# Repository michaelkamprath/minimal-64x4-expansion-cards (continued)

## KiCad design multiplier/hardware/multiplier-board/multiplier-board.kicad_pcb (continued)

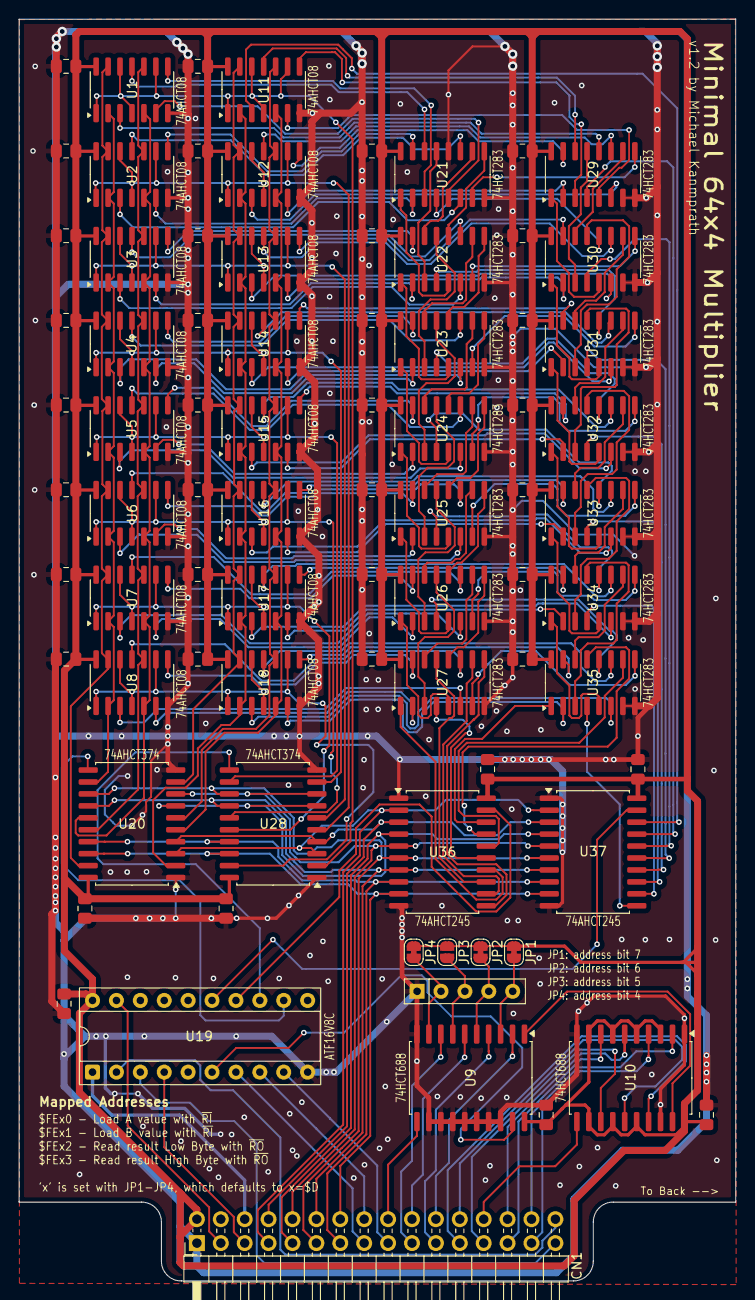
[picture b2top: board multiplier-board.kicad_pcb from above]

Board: 2 copper layers, 76.2 x 134.1 mm, 80 parts (0 on the bottom side), 191 nets.

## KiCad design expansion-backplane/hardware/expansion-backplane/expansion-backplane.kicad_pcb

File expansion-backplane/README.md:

# Expansion Backplane for Minimal 64x4 Computer

This backplane allows connecting of up to 4 expansion cards to the Minimal 64x4 computer. The [expansion connector](./hardware/expansion-connector/) is a convenient way to connect the backplane to the Minimal 64x4 computer.

### Shared `INH` Line
To have multiple cards connected to the backplane, they need to share the active high `INH` inhibit line. If multiple cards are emitting a LOW signal directly, and one emits a HIGH, contention will occur. To prevent such contention, the back plane uses a 74AHCT126 to arbitrate the `INH` signal's progression from a card to the Minimal 64x4's exansion port. Each of the buffers in the 74AHCT126 have their input signal tied high, and the each card's `INH` output us used to control the output enable for it's assigned buffer. In this way, when a card's `INH` output is low (not active), it's corresponding buffer has its output in a high-Z state. So if another card asserts it's `INH` line high, there won't be bus contention back to the card. But each card's active high `INH` signal is passed through to the Minimal 64x4. The downside is that each expansion card cannot monitor whether another card is asserting the `INH` signal. This is not deemed to be a signficant issues since Minimal 64x4 expansion board are generally memory mapped, and thus only one can be actively writing to the bus at a time.

### Card Address Assignment
The data bus has **no arbitration** — the `INH` scheme above protects only the inhibit line. Correctness depends entirely on one card decoding a given address. Because address lines settle at different times during a bus transition, a card can transiently match another card's address and drive the bus against it, so assign base addresses to maximize the **Hamming distance of the decoded address bits**, not the hex separation.

| Card | Base | Decoded `A7..A3` |
| --- | --- | --- |
| Multiplier | `$FED0` | `11010` |
| Timer | `$FE28` | `00101` |

**Failure signature** (seen 2026-08 with the timer at `$FEF0`, one bit from the multiplier): reads from the victim card return wrong values intermittently, writes and RAM are fine, results vary run to run *and* between builds as code shifts, and software-only builds are perfect. Diagnose by moving one card, not by debugging the software.

Two mechanisms produce this and are **not yet distinguished**: address-line skew, or the 74HCT688 comparator glitching its output during input transitions. If it's the latter, bit distance is only probabilistic protection and a gated `/G` or delayed enable is needed. To measure: reinstate the colliding address, run `multiplier/software/test_karatsuba_layers.min64x4` (fails ~30% of 65536 cases, so events are continuous), and trigger a logic analyzer on *the victim card's decode asserting while the address belongs to the other card*.

Note that CLK-gating a card's read output enable is **not** a fix: the address and `RI`/`RO` are set on the falling edge and the selected card must be driving the bus before the rising edge latches it, so the read enable has to be live during the settling window by design.

### Power Barrel Jack
The back plane provides a convenient standard 2.1 mm barrel jack you may use to connect to a regulated `5V` power supply to power the expansion cards and additionally power the Minimal 64x4 computer. If this barrel jack is connected to power, be sure to not connect the UART's `+5V` line to the Minimal 64x4 (still connect `GND`)

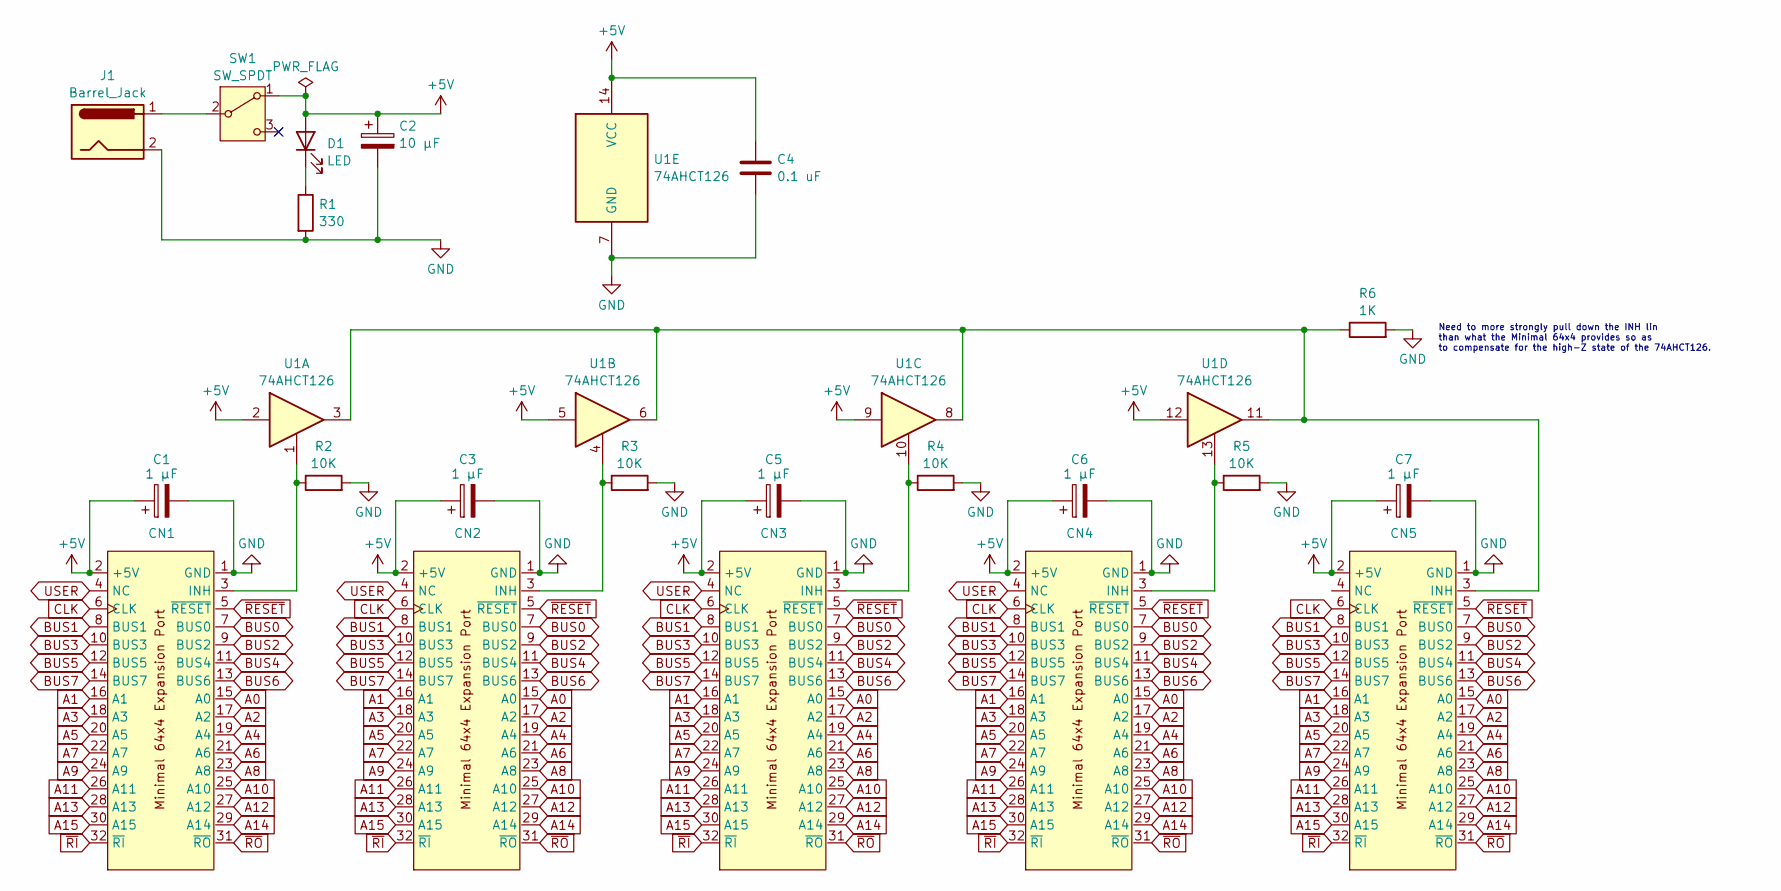
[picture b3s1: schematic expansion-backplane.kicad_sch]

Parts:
C1, C3, C5, C6, C7: 1 µF; CP_Radial_D4.0mm_P2.00mm
C2: 10 µF; CP_Radial_D5.0mm_P2.00mm
C4: 0.1 uF; C_Disc_D3.8mm_W2.6mm_P2.50mm
CN1, CN2, CN3, CN4, CN5: PinSocket_2x16_P2.54mm_Vertical
D1: LED; LED_D3.0mm
J1: Barrel_Jack; BarrelJack_Horizontal
R1: 330; R_Axial_DIN0207_L6.3mm_D2.5mm_P7.62mm_Horizontal
R2, R3, R4, R5: 10K; R_Axial_DIN0207_L6.3mm_D2.5mm_P7.62mm_Horizontal
R6: 1K; R_Axial_DIN0207_L6.3mm_D2.5mm_P7.62mm_Horizontal
SW1: SW_SPDT; E-Switch_200MSP1T2B2M6RE
U1: 74AHCT126; DIP-14_W7.62mm

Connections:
+5V: C1.1, C2.1, C3.1, C4.1, C5.1, C6.1, C7.1, CN1.2 (+5V), CN2.2 (+5V), CN3.2 (+5V), CN4.2 (+5V), CN5.2 (+5V), D1.2 (A), SW1.1 (A), U1.2, U1.5, U1.9, U1.12, U1.14 (VCC)
A0: CN1.15 (A0), CN2.15 (A0), CN3.15 (A0), CN4.15 (A0), CN5.15 (A0)
A1: CN1.16 (A1), CN2.16 (A1), CN3.16 (A1), CN4.16 (A1), CN5.16 (A1)
A2: CN1.17 (A2), CN2.17 (A2), CN3.17 (A2), CN4.17 (A2), CN5.17 (A2)
A3: CN1.18 (A3), CN2.18 (A3), CN3.18 (A3), CN4.18 (A3), CN5.18 (A3)
A4: CN1.19 (A4), CN2.19 (A4), CN3.19 (A4), CN4.19 (A4), CN5.19 (A4)
A5: CN1.20 (A5), CN2.20 (A5), CN3.20 (A5), CN4.20 (A5), CN5.20 (A5)
A6: CN1.21 (A6), CN2.21 (A6), CN3.21 (A6), CN4.21 (A6), CN5.21 (A6)
A7: CN1.22 (A7), CN2.22 (A7), CN3.22 (A7), CN4.22 (A7), CN5.22 (A7)
A8: CN1.23 (A8), CN2.23 (A8), CN3.23 (A8), CN4.23 (A8), CN5.23 (A8)
A9: CN1.24 (A9), CN2.24 (A9), CN3.24 (A9), CN4.24 (A9), CN5.24 (A9)
A10: CN1.25 (A10), CN2.25 (A10), CN3.25 (A10), CN4.25 (A10), CN5.25 (A10)
A11: CN1.26 (A11), CN2.26 (A11), CN3.26 (A11), CN4.26 (A11), CN5.26 (A11)
A12: CN1.27 (A12), CN2.27 (A12), CN3.27 (A12), CN4.27 (A12), CN5.27 (A12)
A13: CN1.28 (A13), CN2.28 (A13), CN3.28 (A13), CN4.28 (A13), CN5.28 (A13)
A14: CN1.29 (A14), CN2.29 (A14), CN3.29 (A14), CN4.29 (A14), CN5.29 (A14)
A15: CN1.30 (A15), CN2.30 (A15), CN3.30 (A15), CN4.30 (A15), CN5.30 (A15)
BUS0: CN1.7 (BUS0), CN2.7 (BUS0), CN3.7 (BUS0), CN4.7 (BUS0), CN5.7 (BUS0)
BUS1: CN1.8 (BUS1), CN2.8 (BUS1), CN3.8 (BUS1), CN4.8 (BUS1), CN5.8 (BUS1)
BUS2: CN1.9 (BUS2), CN2.9 (BUS2), CN3.9 (BUS2), CN4.9 (BUS2), CN5.9 (BUS2)
BUS3: CN1.10 (BUS3), CN2.10 (BUS3), CN3.10 (BUS3), CN4.10 (BUS3), CN5.10 (BUS3)
BUS4: CN1.11 (BUS4), CN2.11 (BUS4), CN3.11 (BUS4), CN4.11 (BUS4), CN5.11 (BUS4)
BUS5: CN1.12 (BUS5), CN2.12 (BUS5), CN3.12 (BUS5), CN4.12 (BUS5), CN5.12 (BUS5)
BUS6: CN1.13 (BUS6), CN2.13 (BUS6), CN3.13 (BUS6), CN4.13 (BUS6), CN5.13 (BUS6)
BUS7: CN1.14 (BUS7), CN2.14 (BUS7), CN3.14 (BUS7), CN4.14 (BUS7), CN5.14 (BUS7)
CLK: CN1.6 (CLK), CN2.6 (CLK), CN3.6 (CLK), CN4.6 (CLK), CN5.6 (CLK)
GND: C1.2, C2.2, C3.2, C4.2, C5.2, C6.2, C7.2, CN1.1 (GND), CN2.1 (GND), CN3.1 (GND), CN4.1 (GND), CN5.1 (GND), J1.2, R1.2, R2.2, R3.2, R4.2, R5.2, R6.2, U1.7 (GND)
unnamed: CN1.3 (INH), R2.1, U1.1
unnamed: CN2.3 (INH), R3.1, U1.4
unnamed: CN3.3 (INH), R4.1, U1.10
unnamed: CN4.3 (INH), R5.1, U1.13
unnamed: CN5.3 (INH), R6.1, U1.3, U1.6, U1.8, U1.11
unnamed: D1.1 (K), R1.1
unnamed: J1.1, SW1.2 (B)
USER: CN1.4 (NC), CN2.4 (NC), CN3.4 (NC), CN4.4 (NC)
~RESET: CN1.5 (~RESET), CN2.5 (~RESET), CN3.5 (~RESET), CN4.5 (~RESET), CN5.5 (~RESET)
~RI: CN1.32 (~RI), CN2.32 (~RI), CN3.32 (~RI), CN4.32 (~RI), CN5.32 (~RI)
~RO: CN1.31 (~RO), CN2.31 (~RO), CN3.31 (~RO), CN4.31 (~RO), CN5.31 (~RO)

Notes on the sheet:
Need to more strongly pull down the INH lin than what the Minimal 64x4 provides so as to compensate for the high-Z state of the 74AHCT126.

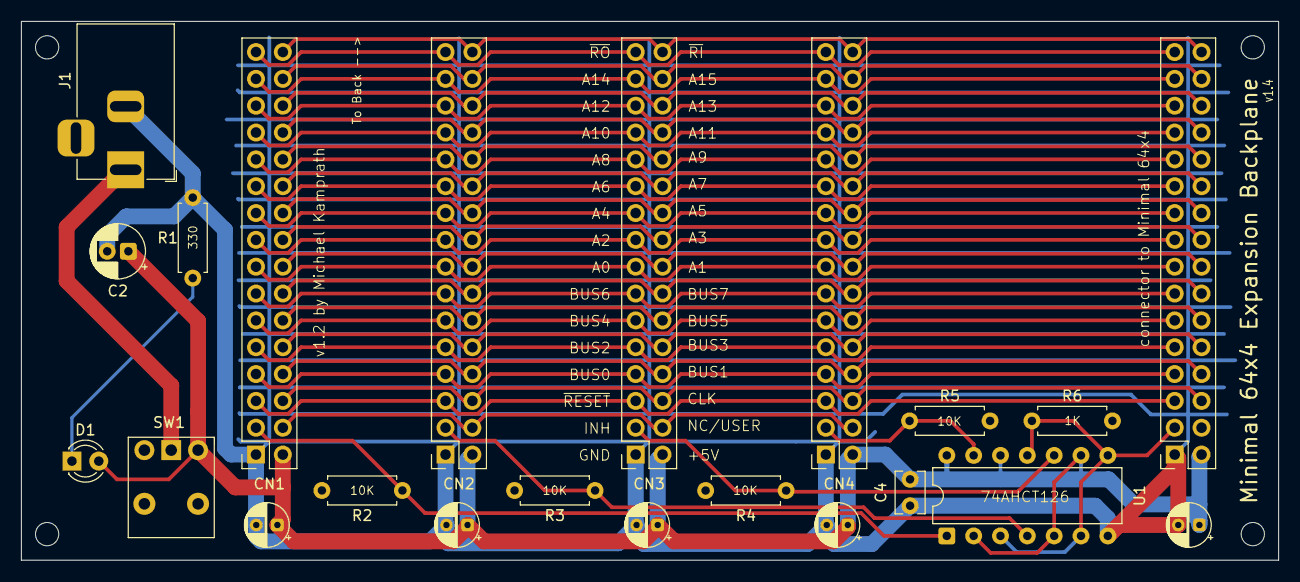
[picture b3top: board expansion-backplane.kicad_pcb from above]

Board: 2 copper layers, 119.0 x 51.0 mm, 22 parts (0 on the bottom side), 38 nets.

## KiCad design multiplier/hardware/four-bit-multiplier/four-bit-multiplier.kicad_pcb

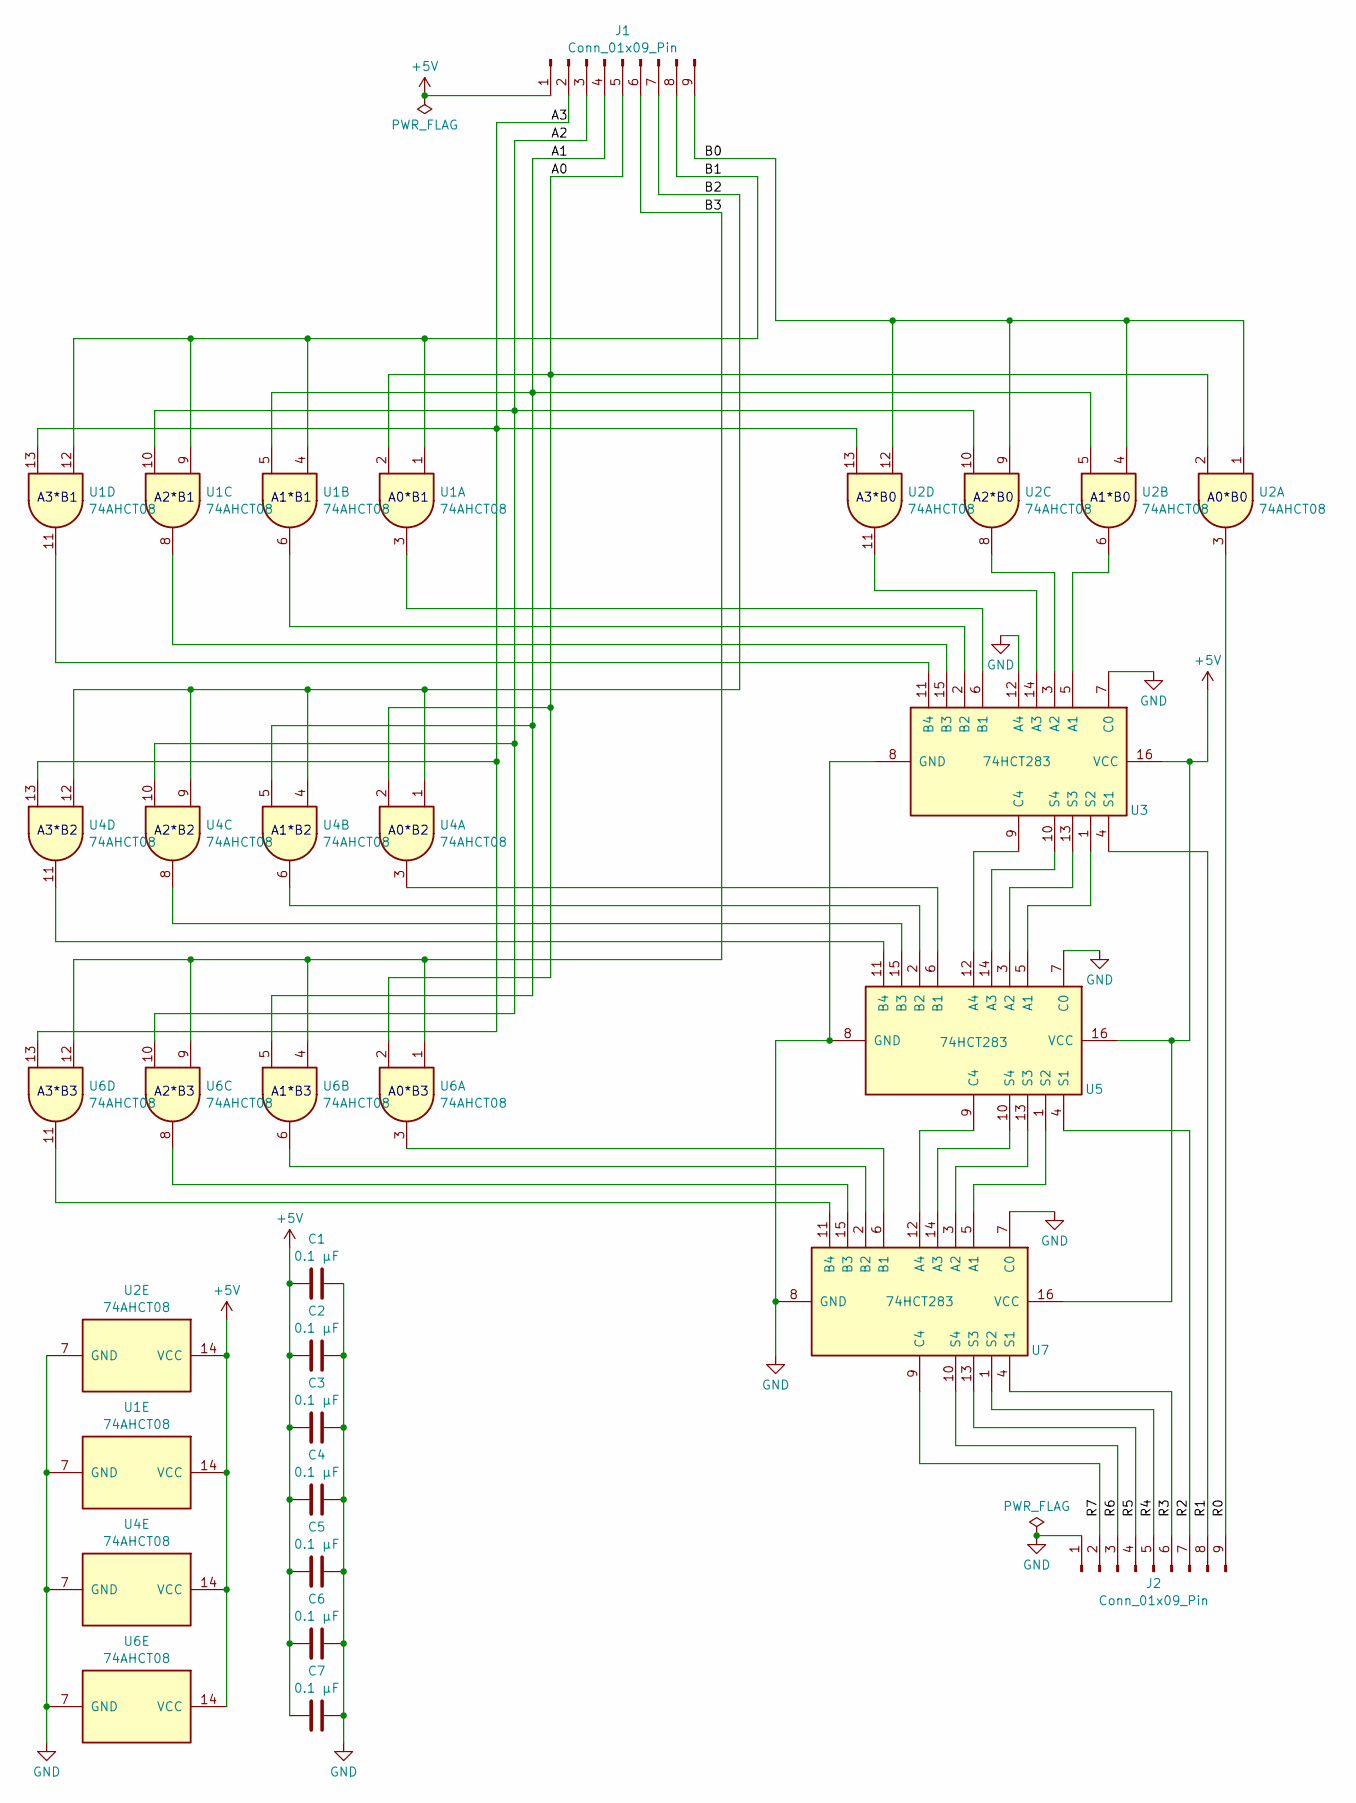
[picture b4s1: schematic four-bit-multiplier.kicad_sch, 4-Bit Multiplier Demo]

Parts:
C1, C2, C3, C4, C5, C6, C7: 0.1 µF; C_0805_2012Metric_Pad1.18x1.45mm_HandSolder
J1, J2: Conn_01x09_Pin; PinHeader_1x09_P2.54mm_Vertical
U1, U2, U4, U6: 74AHCT08; SOIC-14_3.9x8.7mm_P1.27mm
U3, U5, U7: 74HCT283; SOIC-16_3.9x9.9mm_P1.27mm

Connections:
+5V: C1.1, C2.1, C3.1, C4.1, C5.1, C6.1, C7.1, J1.1, U1.14 (VCC), U2.14 (VCC), U3.16 (VCC), U4.14 (VCC), U5.16 (VCC), U6.14 (VCC), U7.16 (VCC)
/A0: J1.5, U1.2, U2.2, U4.2, U6.2
/A1: J1.4, U1.5, U2.5, U4.5, U6.5
/A2: J1.3, U1.10, U2.10, U4.10, U6.10
/A3: J1.2, U1.13, U2.13, U4.13, U6.13
/B0: J1.9, U2.1, U2.4, U2.9, U2.12
/B1: J1.8, U1.1, U1.4, U1.9, U1.12
/B2: J1.7, U4.1, U4.4, U4.9, U4.12
/B3: J1.6, U6.1, U6.4, U6.9, U6.12
/R0: J2.9, U2.3
/R1: J2.8, U3.4 (S1)
/R2: J2.7, U5.4 (S1)
/R3: J2.6, U7.4 (S1)
/R4: J2.5, U7.1 (S2)
/R5: J2.4, U7.13 (S3)
/R6: J2.3, U7.10 (S4)
/R7: J2.2, U7.9 (C4)
GND: C1.2, C2.2, C3.2, C4.2, C5.2, C6.2, C7.2, J2.1, U1.7 (GND), U2.7 (GND), U3.7 (C0), U3.8 (GND), U3.12 (A4), U4.7 (GND), U5.7 (C0), U5.8 (GND), U6.7 (GND), U7.7 (C0), U7.8 (GND)
unnamed: U2.6, U3.5 (A1)
unnamed: U2.8, U3.3 (A2)
unnamed: U2.11, U3.14 (A3)
unnamed: U1.3, U3.6 (B1)
unnamed: U1.6, U3.2 (B2)
unnamed: U1.8, U3.15 (B3)
unnamed: U1.11, U3.11 (B4)
unnamed: U3.9 (C4), U5.12 (A4)
unnamed: U3.1 (S2), U5.5 (A1)
unnamed: U3.13 (S3), U5.3 (A2)
unnamed: U3.10 (S4), U5.14 (A3)
unnamed: U4.3, U5.6 (B1)
unnamed: U4.6, U5.2 (B2)
unnamed: U4.8, U5.15 (B3)
unnamed: U4.11, U5.11 (B4)
unnamed: U5.9 (C4), U7.12 (A4)
unnamed: U5.1 (S2), U7.5 (A1)
unnamed: U5.13 (S3), U7.3 (A2)
unnamed: U5.10 (S4), U7.14 (A3)
unnamed: U6.3, U7.6 (B1)
unnamed: U6.6, U7.2 (B2)
unnamed: U6.8, U7.15 (B3)
unnamed: U6.11, U7.11 (B4)

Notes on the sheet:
A3*B3
A1*B2
A1*B0
A0*B0
A2*B2
A2*B1
A1*B1
A1*B3
A2*B0
A3*B2
A2*B3
A0*B3
A3*B1
A3*B0
A0*B2
A0*B1

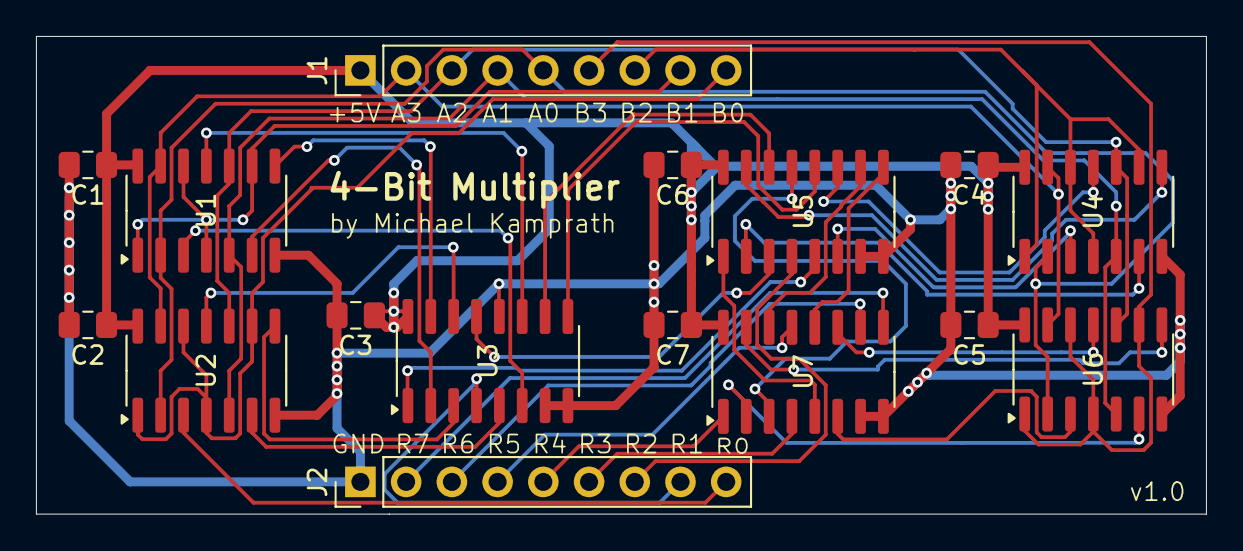
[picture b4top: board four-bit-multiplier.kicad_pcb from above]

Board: 2 copper layers, 65.0 x 26.5 mm, 16 parts (0 on the bottom side), 41 nets.

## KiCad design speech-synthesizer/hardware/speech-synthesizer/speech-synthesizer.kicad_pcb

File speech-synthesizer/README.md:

# TMS5220 Speech Synthesizer for Minimal 64x4 Computer
This project creates a TMS5220-based speech synthesizer board for the [Minimal 64x4](https://github.com/slu4coder/Minimal-64x4-Home-Computer) expansion port. The high-level design criteria are:

1. **Accommodate the “slow memory” nature of the TMS5220** by using hardware to buffer the interactions between the CPU and the TMS5220 such that the CPU is free to do other tasks while the TMS5220 processes data. This contrasts with typical 1980s computer hardware designs, which would halt the CPU while the TMS5220 processed data.
2. **Only support “external” speech data; PHROMs are not supported.** Not supporting PHROMs greatly simplifies the board and saves money, as original PHROMs are hard to come by in the modern age. Most games of the 1980s did not use PHROM data, instead providing their own LPC-encoded speech data.

This board supports both the TMS5220 and TMS5220C variants of the speech synthesizer chip.

## Hardware Design
The board responds to three memory-mapped addresses (the board is adjustable to set the `_` value below, but it defaults to `0xC`):

* `0xFE_0` – **TMS5220 Command Register**
  This address allows the host computer to write data to the TMS5220’s command register, which is used for sending “external speech” data to the TMS5220. In general, the host computer will write certain TMS5220 commands and speech data to this address.

* `0xFE_1` – **TMS5220 Status Register**
  This address allows the host computer to fetch the internal TMS5220 status register. To do that, the host computer writes some data to this address (any value, as the value is not actually used) to start the sequence of events to get the internal status from the TMS5220. When this is done, the status value will be readable by the host computer at this address. The status data being ready is indicated by the board’s `BUSY` line, which is readable at the **Board Status Register**. The `BUSY` line will be asserted high from the moment this address is written to until the status value is ready to be read.

* `0xFE_2` – **Board Status Register**
  This address exposes several internal states of this board, independent of the TMS5220, and can be read by the host computer at any time. The individual bits within the byte value read are below. Of these lines, the host computer generally only interacts with the `/INT` and `BUSY` bits.

  * **bit 0 – `BUSY`**
    Indicates whether the TMS5220 or the board, in general, is working on something. The host computer should not interact with the TMS5220 Command or Status registers while this bit is high.
  * **bit 1 – `/INT`**
    The current value of the active-low interrupt line coming out of the TMS5220. When this bit is low, it indicates that the TMS5220 requires attention. The specific issue can be determined by reading the TMS5220 Status Register.
  * **bit 2 – `/READY`**
    The current value of the active-low `READY` line out of the TMS5220. Host computer software should use the `BUSY` line to arbitrate interaction with the board, but the `READY` line is exposed here for diagnostic purposes.
  * **bit 3 – `WS`**
    The current status of the `WS` flip flop (active high). Exposed for diagnostic purposes.
  * **bit 4 – `RS`**
    The current status of the `RS` flip flop (active high). Exposed for diagnostic purposes.

* `0xFE_3` – **TMS5220C Reset** – *Currently Unimplemented*
  The TMS5220C variant can be reset by holding both the `/RS` and `/WS` lines low at the same time. This action has undefined results for the non-C TMS5220 variant.

### TMS5220 “Slow Memory” Issue
A key pin to understand on the TMS5220 is the `READY` signal at pin 18. The TMS5220 drives the `READY` pin low when it is ready to accept input or provide output to the host computer. When the `READY` pin is high, the TMS5220 is busy processing data and does not immediately act on—if not outright ignore—any interactions the CPU initiates. In many 1980s-era computers, the `READY` pin was connected to the CPU’s halt or wait-state pin, causing the CPU to stop while the TMS5220 processed data. This board takes a different approach. In some ways, this is necessary because the Minimal 64x4 has no line that would allow an accessory to pause or halt the CPU. However, this design choice is otherwise agnostic of that limitation.

As a result, data interactions between the host computer and the TMS5220 must be cached to handle the timing differences. The key to caching these CPU interactions is the ATF22V10C programmable logic chip and the 74HCT74 flip flops. The flip flops hold the `/WS` and `/RS` signals on the TMS5220, and the ATF22V10C is programmed to create a state machine that manages these flip flops. For example, here is the sequence of events for writing a byte of data to the TMS5220:

1. When the address bus is set to the memory-mapped address of `0xFEC0`, the 74HCT688s will assert this `MMAP` line, and the `M0` and `M1` address lines will be 0. To write to the TMS5220, the host computer `/RI` line will be asserted. The ATF22V10C’s programmable logic then asserts `WS_CLK`, which is the clock line that drives the `WS` flip flop, in turn asserting the active-low `/WS` line to the TMS5220. This tells the TMS5220 that we want to write data to its data lines.
2. At the same time `WS_CLK` causes the `WS` flip flop to set its state, `WS_CLK` also causes the data bus input 74HCT374 flip flop to load the contents of the host computer’s data bus. Because of this, the expansion board can capture and hold the data bus value the host computer is writing to the TMS5220, allowing the host computer to move on to other tasks while this flip flop holds the data bus value. Furthermore, the `/WS` line to the TMS5220 also drives the output enable on the 74HCT374 octal flip flop, so the buffered data will be held and driven onto the board’s internal data bus for the entire time `/WS` is low—even as the host computer does other work. This is the essence of the “slow memory” issue: the TMS5220 requires several host-computer clock cycles to read in the data, and its data lines must be held for the entire duration. The 74HCT374 flip flop buffers the data and holds the lines active as long as needed.
3. In response to the `/WS` line being asserted, the TMS5220 drives the `READY` line high. When this occurs, the ATF22V10C waits until the `READY` line transitions from high to low, which indicates that the TMS5220 has finished processing the input data. When the `READY` line goes low, the ATF22V10C then asserts `WS_RST`, the reset line for the `WS` flip flop. This brings `/WS` high, which tells the TMS5220 that the write operation is complete. It also disables the output enable on the 74HCT374 that was buffering the data. In this way, `/WS` remains asserted until the TMS5220 indicates it is done reading the data from the buffers, as indicated by the `READY` line.
4. During this entire sequence, the ATF22V10C asserts the `BUSY` line for the board, which can be read by the host computer at address `0xFE_2` via the 74HCT245. This allows the host computer to query the board to see if the TMS5220 is done processing data.

A similar sequence is used when reading data from the TMS5220, centered around the `/RS` line.

### Undocumented Timing Issues
The TMS5220 appears to have some timing requirements that are not documented in its datasheet. These requirements were exposed by the Minimal 64x4, which runs at a clock speed faster than the typical host computers for which the TMS5220 was designed. These undocumented timing requirements were determined empirically and could likely be tweaked further:

* **Read Cycle for Status Transfers to External Speech Data Write**
  The datasheet indicates that the `t_wait` after `/RS` goes high is 12 µs. However, I found that something closer to 175 µs was needed between a status read and a subsequent external speech data write.

* **External Speech Data Write to Read Cycle for Status Transfers**
  Similarly, extra time is needed between writing external speech data and then reading the TMS5220 status. Again, I found that about 175 µs was needed.

These values were “tweaked until it worked.” The issues seem related to switching modes of interaction with the TMS5220. By contrast, writing an external speech data byte after a prior external speech data byte does adhere to the timing diagrams in the TMS5220 datasheet. Further experimentation might uncover better or smaller delays for these undocumented requirements.

## Software Design
The provided `speechlib.min64x4` file contains all the subroutines needed to use this board on the Minimal 64x4 home computer:

* `speech_init`
  Call this to initialize the board.

* `speak_synchronous`
  Speaks the LPC data in a passed buffer synchronously. Push the following arguments on the stack (in push order):
  1. **Buffer End Address** – 2-byte end address of the data buffer
  2. **Buffer Start Address** – 2-byte start address of the data buffer

* `speech_start`
  Speaks the LPC data in a passed buffer asynchronously, after synchronously waiting for any currently active talking to finish. Push the following arguments on the stack (in push order):
  1. **Buffer End Address** – 2-byte end address of the data buffer
  2. **Buffer Start Address** – 2-byte start address of the data buffer

* `speech_start_if_not_talking`
  Speaks the LPC data in a passed buffer asynchronously if there is no currently active speech. Push the following arguments on the stack (in push order):
  1. **Buffer End Address** – 2-byte end address of the data buffer
  2. **Buffer Start Address** – 2-byte start address of the data buffer

* `speech_update_buffer`
  Call this periodically (about every 1 ms) to enable asynchronous speech. No arguments.

* `speech_get_status`
  Gets the contents of the TMS5220 status register, which is returned in the `A` register. The following bit masks are defined to help interpret the results:
  * `SPEECH_STATUS_TALK` – The TMS5220 is currently talking.
  * `SPEECH_STATUS_BUFFER_LOW` – The TMS5220 FIFO buffer is half-empty. More LPC data needs to be sent.
    *_Note_*: The `speech_update_buffer` function automatically updates the FIFO if needed.
  * `SPEECH_STATUS_BUFFER_EMPTY` – The TMS5220 FIFO buffer is empty.

# Compiling the Software
All software found in the [software](./software/) directory is compiled with [BespokeASM](https://github.com/michaelkamprath/bespokeasm), which supports the Minimal 64x4. [Carsten Herting](https://github.com/slu4coder), the creator of the Minimal 64x4, also provides an assembler for it, but that assembler is quite minimal. One key shortcoming is the inability to import library code into the current compilation. BespokeASM enables importing libraries and includes several other features that this project’s software depends on.

To compile the speech code in this repository, use the following command:

```sh
bespokeasm compile -c /path/to/bespokeasm/examples/slu4-minimal-64x4/slu4-minimal-64x4.yaml -n -p -t intel_hex lpc_player.min64x4
```
Where `/path/to/bespokeasm` is the path to the BespokeASM repository on your computer. This will produce an Intel HEX representation of the compiled program, which can then be sent to the Minimal 64x4 using its `receive` command.

# Resources
The following resources I found useful when putting together this project

* [TMS5220 Datasheet](./datasheets/tms5220.pdf) - Always consult the datasheet first.
* [Thierry Nouspikel's "The Speech Synthesizer module"](https://www.unige.ch/medecine/nouspikel/ti99/speech.htm) - A detailed overview of how the TMS5220 is used in the TI 99/4a.
* [TI 99/4a Development forum on AtariAge](https://forums.atariage.com/topic/352156-looking-for-help-on-tms5220-circuit-software-design-and-usage/) - These folks are legends, helpful and knowledgable about anything related to Texas Instruments.

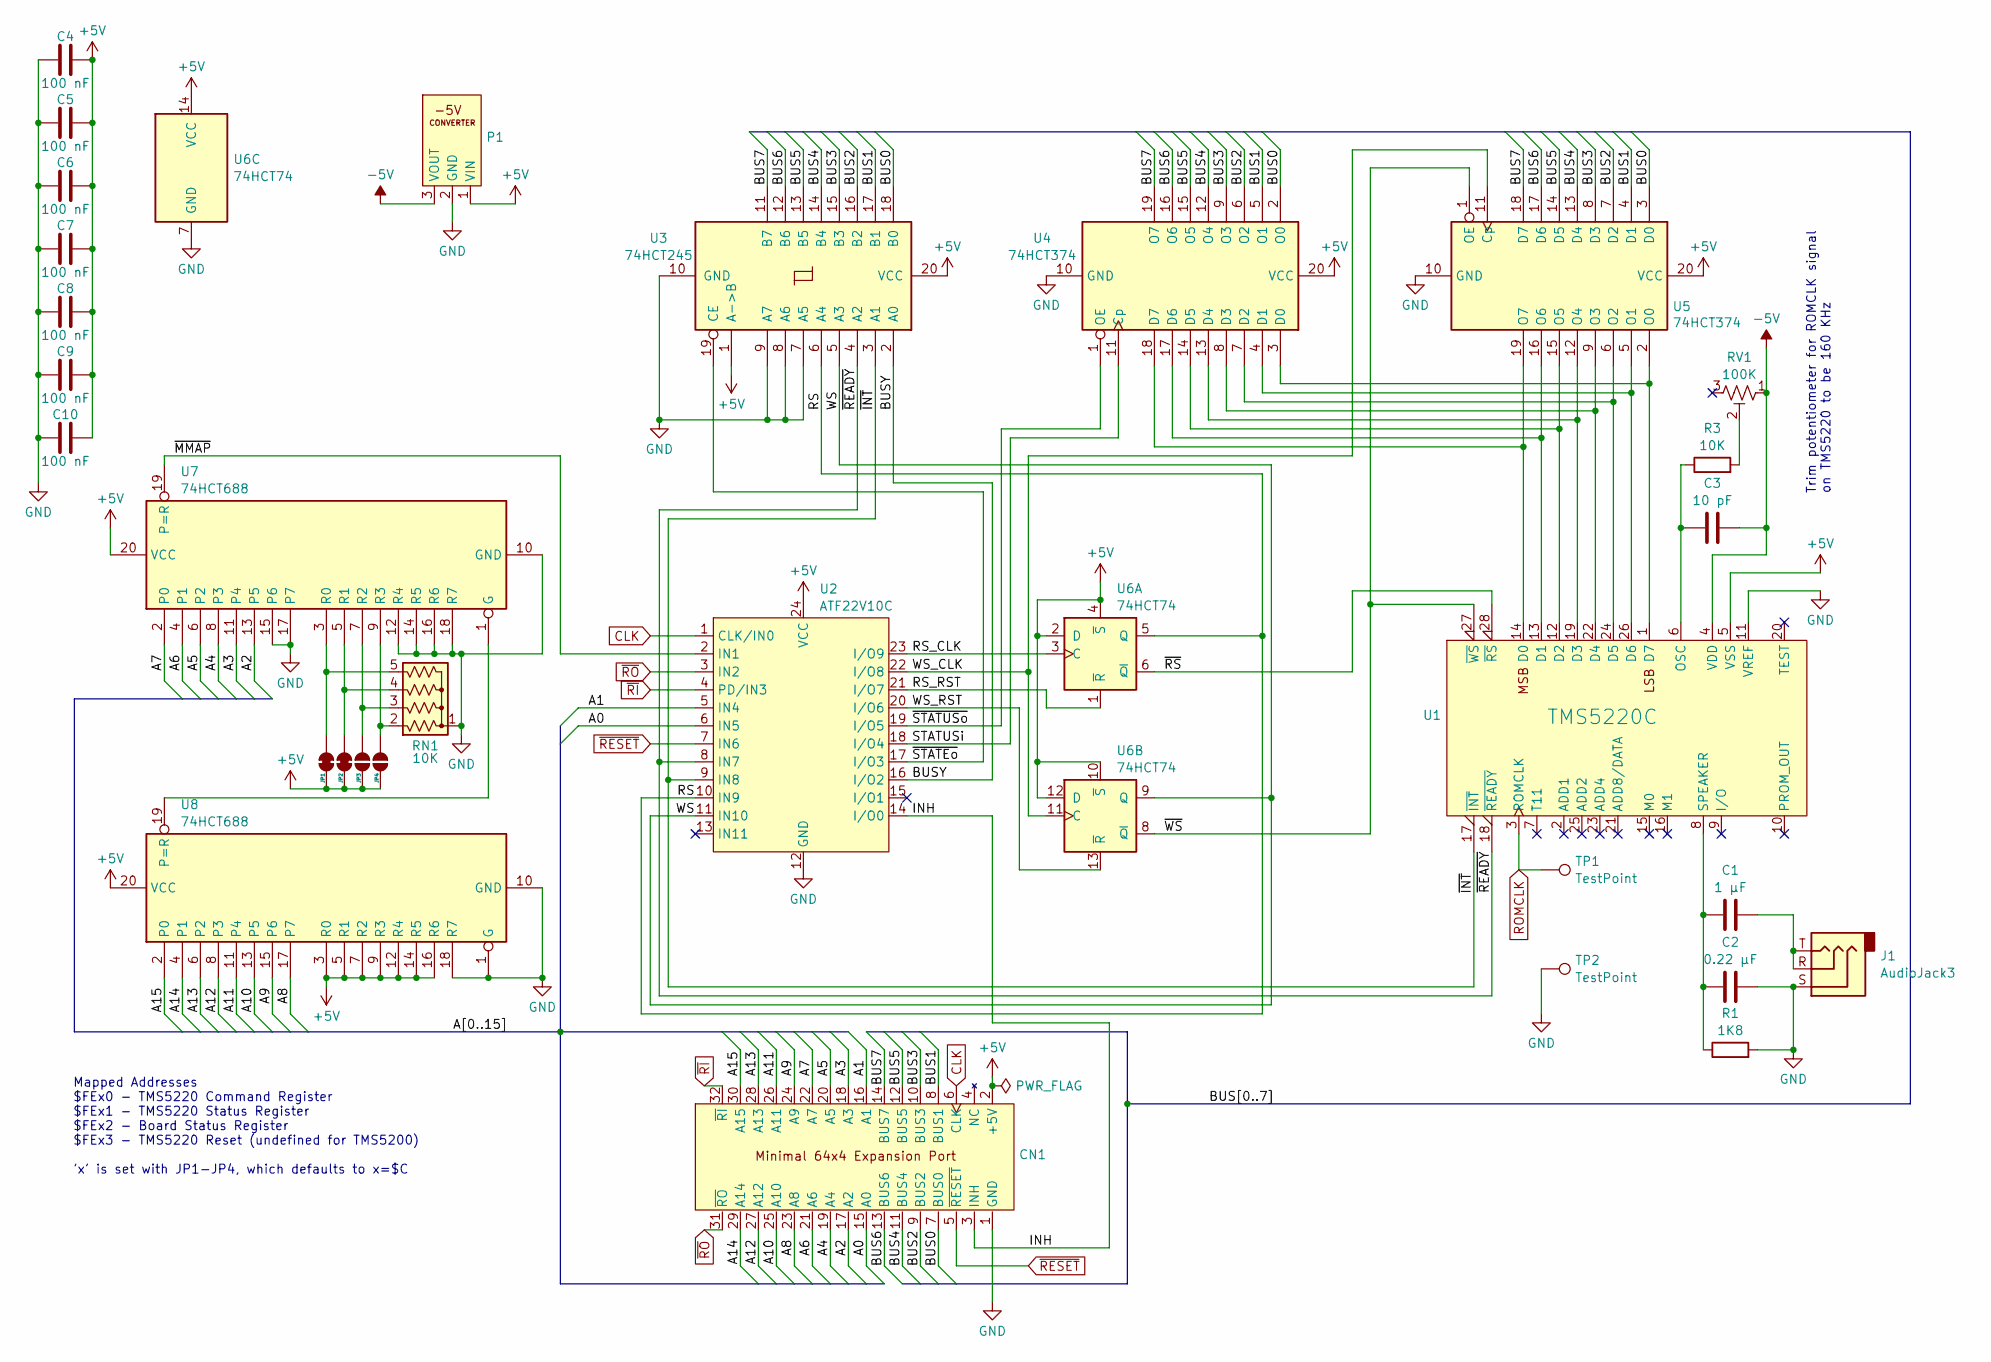
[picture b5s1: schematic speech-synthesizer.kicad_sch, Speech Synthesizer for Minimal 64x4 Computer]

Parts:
C1: 1 µF; C_Disc_D4.7mm_W2.5mm_P5.00mm
C2: 0.22 µF; C_Disc_D4.7mm_W2.5mm_P5.00mm
C3: 10 pF; C_Disc_D5.0mm_W2.5mm_P2.50mm
C4, C5, C6, C7, C8, C9, C10: 100 nF; C_Disc_D3.4mm_W2.1mm_P2.50mm
CN1: PinHeader_2x16_P2.54mm_Horizontal
J1: AudioJack3; Jack_3.5mm_CUI_SJ1-3523N_Horizontal
JP1, JP2: SolderJumper_2_Bridged; SolderJumper-2_P1.3mm_Bridged_RoundedPad1.0x1.5mm
JP3, JP4: SolderJumper_2_Open; SolderJumper-2_P1.3mm_Open_RoundedPad1.0x1.5mm
P1: -5V_Converter
R1: 1K8; R_Axial_DIN0207_L6.3mm_D2.5mm_P10.16mm_Horizontal
R3: 10K; R_Axial_DIN0207_L6.3mm_D2.5mm_P10.16mm_Horizontal
RN1: 10K; R_Array_SIP5
RV1: 100K; Potentiometer_Vishay_T73YP_Vertical
TP1, TP2: TestPoint; TestPoint_Pad_D2.0mm
U1: TMS5220C; DIP-28_W15.24mm_Socket
U2: ATF22V10C; DIP-24_W7.62mm_Socket
U3: 74HCT245; DIP-20_W7.62mm_Socket
U4, U5: 74HCT374; DIP-20_W7.62mm_Socket
U6: 74HCT74; DIP-14_W7.62mm_Socket
U7, U8: 74HCT688; DIP-20_W7.62mm_Socket

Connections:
+5V: C4.2, C5.2, C6.2, C7.2, C8.2, C9.2, C10.2, CN1.2 (+5V), JP1.1 (A), JP2.1 (A), JP3.1 (A), JP4.1 (A), P1.1 (VIN), U1.5 (VSS), U2.24 (VCC), U3.1 (A->B), U3.20 (VCC), U4.20 (VCC), U5.20 (VCC), U6.2 (D), U6.4 (~S), U6.10 (~S), U6.12 (D), U6.14 (VCC), U7.20 (VCC), U8.3 (R0), U8.5 (R1), U8.7 (R2), U8.9 (R3), U8.12 (R4), U8.14 (R5), U8.16 (R6), U8.20 (VCC)
-5V: C3.1, P1.3 (VOUT), RV1.1, U1.4 (VDD)
/A0: CN1.15 (A0), U2.6 (IN5)
/A1: CN1.16 (A1), U2.5 (IN4)
/A2: CN1.17 (A2), U7.13 (P5)
/A3: CN1.18 (A3), U7.11 (P4)
/A4: CN1.19 (A4), U7.8 (P3)
/A5: CN1.20 (A5), U7.6 (P2)
/A6: CN1.21 (A6), U7.4 (P1)
/A7: CN1.22 (A7), U7.2 (P0)
/A8: CN1.23 (A8), U8.17 (P7)
/A9: CN1.24 (A9), U8.15 (P6)
/A10: CN1.25 (A10), U8.13 (P5)
/A11: CN1.26 (A11), U8.11 (P4)
/A12: CN1.27 (A12), U8.8 (P3)
/A13: CN1.28 (A13), U8.6 (P2)
/A14: CN1.29 (A14), U8.4 (P1)
/A15: CN1.30 (A15), U8.2 (P0)
/BUS0: CN1.7 (BUS0), U3.18 (B0), U4.2 (O0), U5.3 (D0)
/BUS1: CN1.8 (BUS1), U3.17 (B1), U4.5 (O1), U5.4 (D1)
/BUS2: CN1.9 (BUS2), U3.16 (B2), U4.6 (O2), U5.7 (D2)
/BUS3: CN1.10 (BUS3), U3.15 (B3), U4.9 (O3), U5.8 (D3)
/BUS4: CN1.11 (BUS4), U3.14 (B4), U4.12 (O4), U5.13 (D4)
/BUS5: CN1.12 (BUS5), U3.13 (B5), U4.15 (O5), U5.14 (D5)
/BUS6: CN1.13 (BUS6), U3.12 (B6), U4.16 (O6), U5.17 (D6)
/BUS7: CN1.14 (BUS7), U3.11 (B7), U4.19 (O7), U5.18 (D7)
/BUSY: U2.16 (I/O2), U3.2 (A0)
/INH: CN1.3 (INH), U2.14 (I/O0)
/RS: U2.10 (IN9), U3.6 (A4), U6.5 (Q)
/RS_CLK: U2.23 (I/O9), U6.3 (C)
/RS_RST: U2.21 (I/O7), U6.1 (~R)
/STATUSi: U2.18 (I/O4), U4.11 (Cp)
/WS: U2.11 (IN10), U3.5 (A3), U6.9 (Q)
/WS_CLK: U2.22 (I/O8), U5.11 (Cp), U6.11 (C)
/WS_RST: U2.20 (I/O6), U6.13 (~R)
/~INT: U1.17 (~INT), U2.9 (IN8), U3.3 (A1)
/~MMAP: U2.2 (IN1), U7.19 (P=R)
/~READY: U1.18 (~READY), U2.8 (IN7), U3.4 (A2)
/~RS: U1.28 (~RS), U6.6 (~Q)
/~STATEo: U2.17 (I/O3), U3.19 (CE)
/~STATUSo: U2.19 (I/O5), U4.1 (OE)
/~WS: U1.27 (~WS), U5.1 (OE), U6.8 (~Q)
CLK: CN1.6 (CLK), U2.1 (CLK/IN0)
GND: C2.2, C4.1, C5.1, C6.1, C7.1, C8.1, C9.1, C10.1, CN1.1 (GND), J1.S, P1.2 (GND), R1.2, RN1.1 (common), TP2.1, U1.11 (VREF), U2.12 (GND), U3.7 (A5), U3.8 (A6), U3.9 (A7), U3.10 (GND), U4.10 (GND), U5.10 (GND), U6.7 (GND), U7.10 (GND), U7.12 (R4), U7.14 (R5), U7.15 (P6), U7.16 (R6), U7.17 (P7), U7.18 (R7), U8.1 (G), U8.10 (GND), U8.18 (R7)
unnamed: C1.2, J1.R, J1.T
unnamed: JP1.2 (B), RN1.5 (R4), U7.3 (R0)
unnamed: JP2.2 (B), RN1.4 (R3), U7.5 (R1)
unnamed: JP3.2 (B), RN1.3 (R2), U7.7 (R2)
unnamed: JP4.2 (B), RN1.2 (R1), U7.9 (R3)
unnamed: R3.2, RV1.2
unnamed: U1.14 (D0), U4.18 (D7), U5.19 (O7)
unnamed: U1.13 (D1), U4.17 (D6), U5.16 (O6)
unnamed: U1.12 (D2), U4.14 (D5), U5.15 (O5)
unnamed: U1.19 (D3), U4.13 (D4), U5.12 (O4)
unnamed: U1.22 (D4), U4.8 (D3), U5.9 (O3)
unnamed: U1.24 (D5), U4.7 (D2), U5.6 (O2)
unnamed: U1.26 (D6), U4.4 (D1), U5.5 (O1)
unnamed: U1.1 (D7), U4.3 (D0), U5.2 (O0)
unnamed: C3.2, R3.1, U1.6 (OSC)
unnamed: C1.1, C2.1, R1.1, U1.8 (SPEAKER)
unnamed: U7.1 (G), U8.19 (P=R)
ROMCLK: TP1.1, U1.3 (ROMCLK)
~RESET: CN1.5 (~RESET), U2.7 (IN6)
~RI: CN1.32 (~RI), U2.4 (PD/IN3)
~RO: CN1.31 (~RO), U2.3 (IN2)

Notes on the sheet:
Trim potentiometer for ROMCLK signal on TMS5220 to be 160 KHz
Mapped Addresses $FEx0 - TMS5220 Command Register $FEx1 - TMS5220 Status Register $FEx2 - Board Status Register $FEx3 - TMS5220 Reset (undefined for TMS5200) 'x' is set with JP1-JP4, which defaults to x=$C

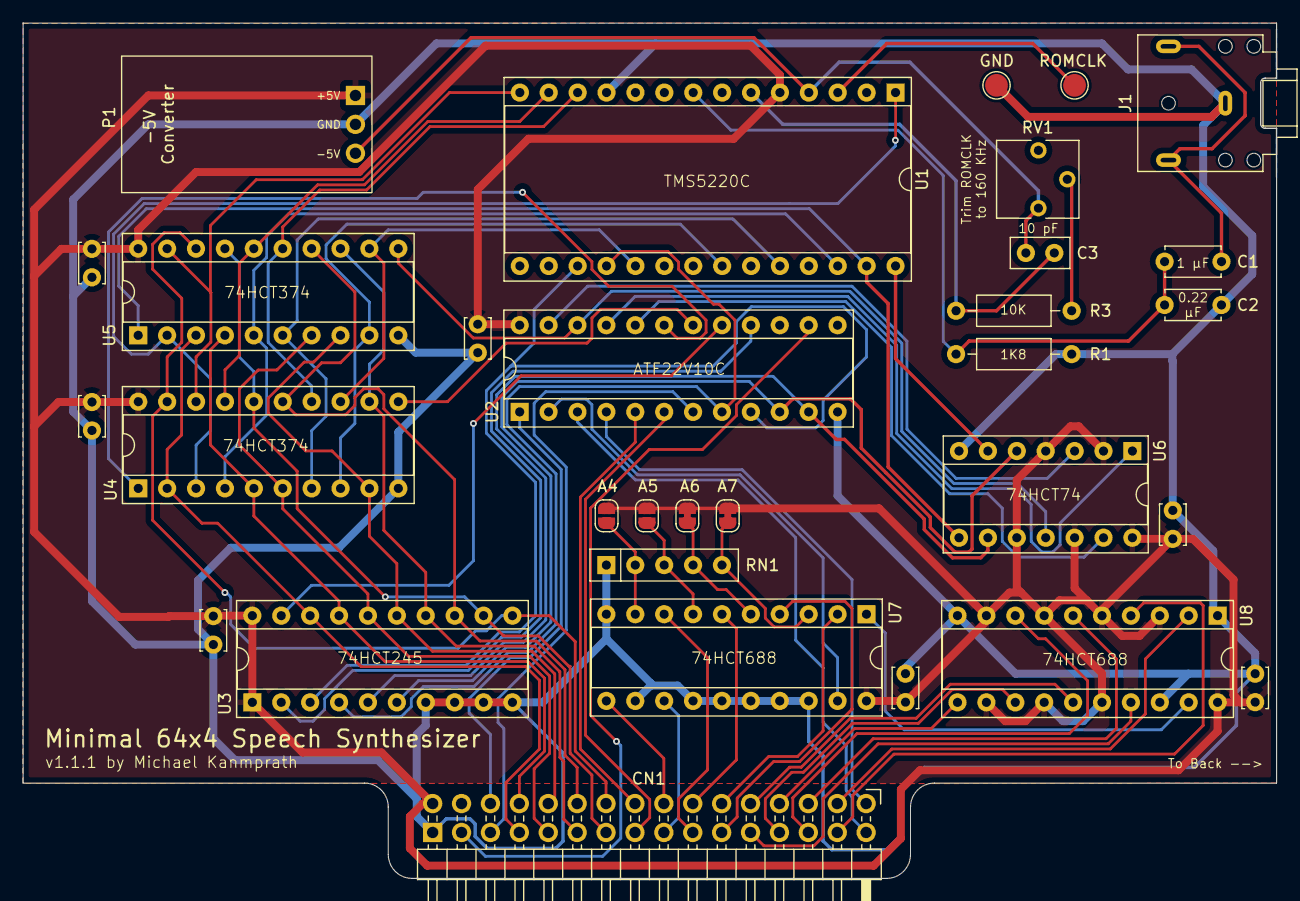
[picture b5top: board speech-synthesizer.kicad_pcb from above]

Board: 2 copper layers, 110.2 x 75.2 mm, 31 parts (0 on the bottom side), 65 nets.

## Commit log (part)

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2024-12-25 added backplane
2024-12-25 speech synthizer setup
2024-12-25 updatedd PCB layouts
2024-12-25 added expansion connector
2024-12-25 tweaked timings
2024-12-25 updated documentation
2024-12-25 added sample code for speech
2024-12-25 created speech pcb
2024-12-25 update speech pld file and more
2024-12-25 first bespokeasm compilable version of invaders
2024-12-25 updated sounds
2024-12-25 improved output format
2024-12-25 improved sounds for speech invaders
2024-12-25 added speech samples
2024-12-25 added lpc player app
2024-12-25 improved backplane
2024-12-25 removed barier mosfet
2024-12-25 added pull down resistors
2024-12-25 tweaks
2024-12-25 typo
2024-12-25 added datasheets
2024-12-29 added is_talking subroutine
2024-12-29 improved silkscreen
2024-12-29 added pull down resistor
2024-12-31 improved documentation
2025-01-01 added BOM
2025-01-04 updated timing
2025-04-11 update kicad version
2025-05-30 tweaked output display
2025-07-04 added wotw speech demo
2025-07-04 first schematice of 4-bit multiplier
2025-07-04 fixed carry
2025-07-26 added .gitignore
2025-08-18 first version of multiplier board
2025-08-18 corrected part designator
2025-08-25 start of software for multiplier board
2025-08-26 added signed integer multiplications
2025-08-27 got mandelbrot working
2025-08-27 improved performance of multiply_i16
2025-08-28 improved performance
2025-08-28 added controller PLD
2025-08-28 linting
2025-08-31 corrected issues
2025-08-31 corrected an error
2025-09-01 added better ground plane
2025-09-02 updated version
2025-09-07 various improvements
2025-09-07 changed pcb to 4-layer with internal ground planes
2025-09-10 improved formatting
2025-09-15 updated syntax for updated bespokeasm
2025-10-07 updated for new bespokeasm
2025-11-28 rotating rectangle demo
2025-11-29 improved rotating rect app
2025-12-14 reverted PLD
2025-12-24 fixed bug
2025-12-24 fixed multiple definitions
2025-12-24 speed improvement
2025-12-24 minor improvements
2026-01-17 improved signal line isolation
2026-01-18 improved signal integrity
2026-01-24 Hardware Multiplier (#1)
    Created a hardware multiplier for the Minimal 64x4
2026-01-29 improvements
2026-01-31 fixed bug with signed right shift
2026-02-02 added Karastuba algorithm demo
2026-02-02 require USE_ACCELERATOR defined
2026-02-02 Karatsuba Demo (#2)
    Added demo and tests of using the Karastuba algorithm to speed up multiplication, even with the hardware multiplier card.
2026-02-03 corrected calculation bug
2026-02-03 added check to ensure test is configured correctly
2026-02-03 refactored and created mathlib64
2026-02-03 Further work on Karastuba implementation (#3)
    Created mathlib64.min64x4 to implement multiplication based on Karastuba algorithm. Also added some tests to ensure algorithm correctness.
2026-02-03 removed redundant compiler message
2026-02-03 added language documentation for AI agent
2026-02-03 typos
2026-02-03 gitignore
2026-02-16 card schematic completed
2026-02-17 timer pcb layout
2026-02-22 created consolidated mathlib
2026-02-22 improved documentation and other fixes
2026-02-28 layout improvements
2026-02-28 corrected design flaw in hardware
2026-03-07 improved karatsuba demo
2026-03-07 improved docs
2026-03-07 Timer Card (#4)
    Adds a clock counting Timer Card.
2026-04-05 improved timer card design
2026-04-20 added Extended Min versions of speech card demos
2026-04-26 reformatted
2026-04-27 updated syntax for xmin v0.5
2026-04-28 xmin speech demos
2026-04-28 small correction
2026-04-30 small tweaks
2026-05-02 improved timer pld
